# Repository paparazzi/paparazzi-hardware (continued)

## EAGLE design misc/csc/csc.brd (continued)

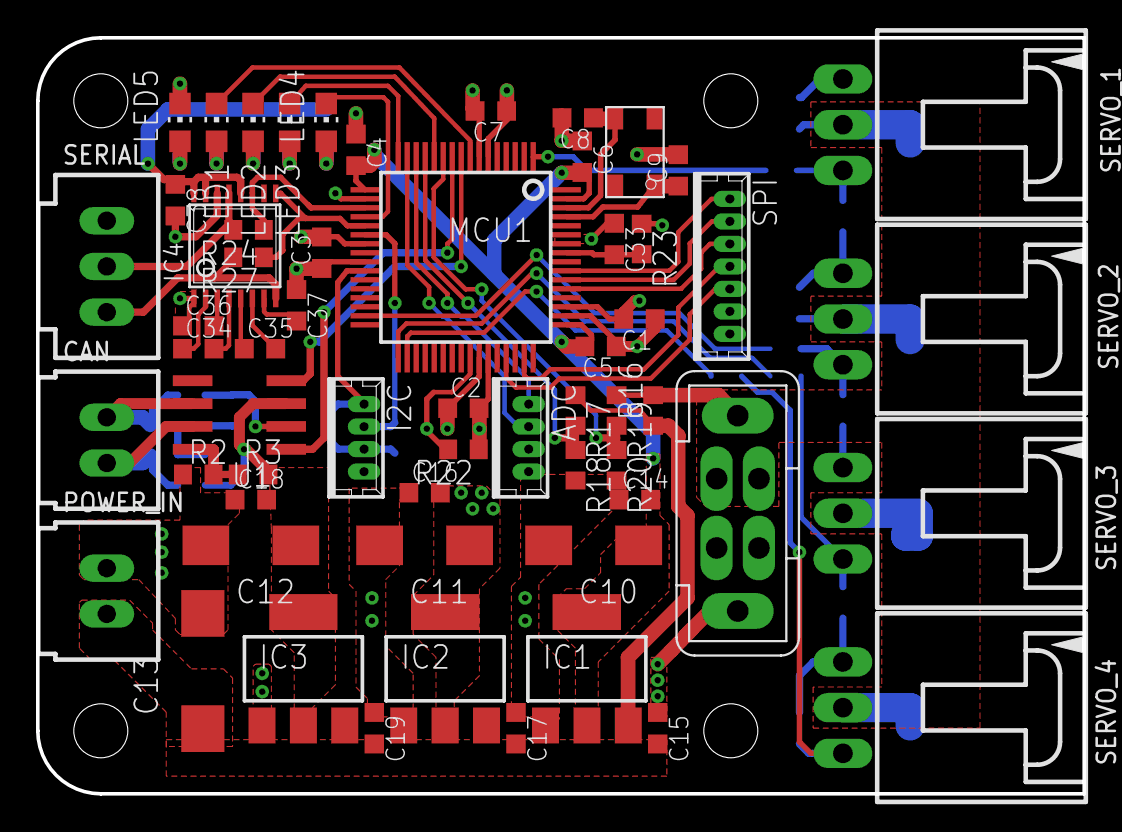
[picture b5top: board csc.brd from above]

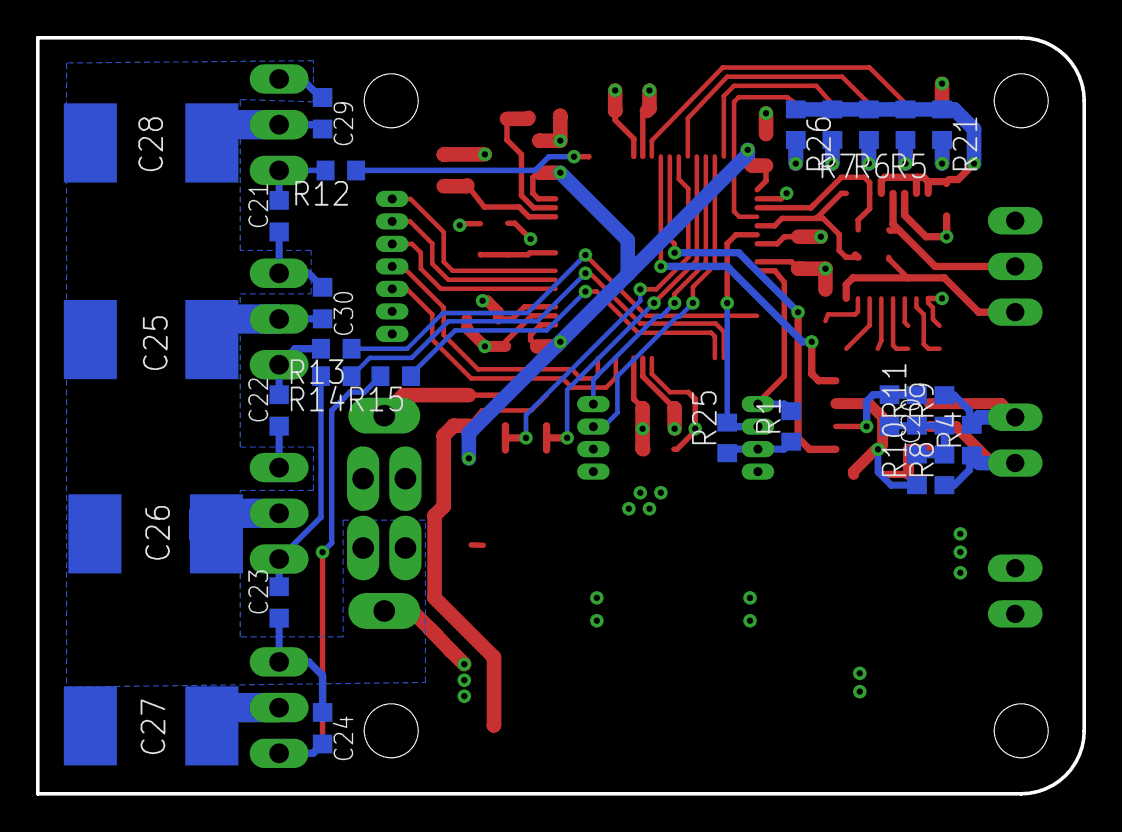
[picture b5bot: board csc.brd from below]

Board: 4 copper layers, 58.1 x 42.0 mm, 87 parts (27 on the bottom side), 55 nets.

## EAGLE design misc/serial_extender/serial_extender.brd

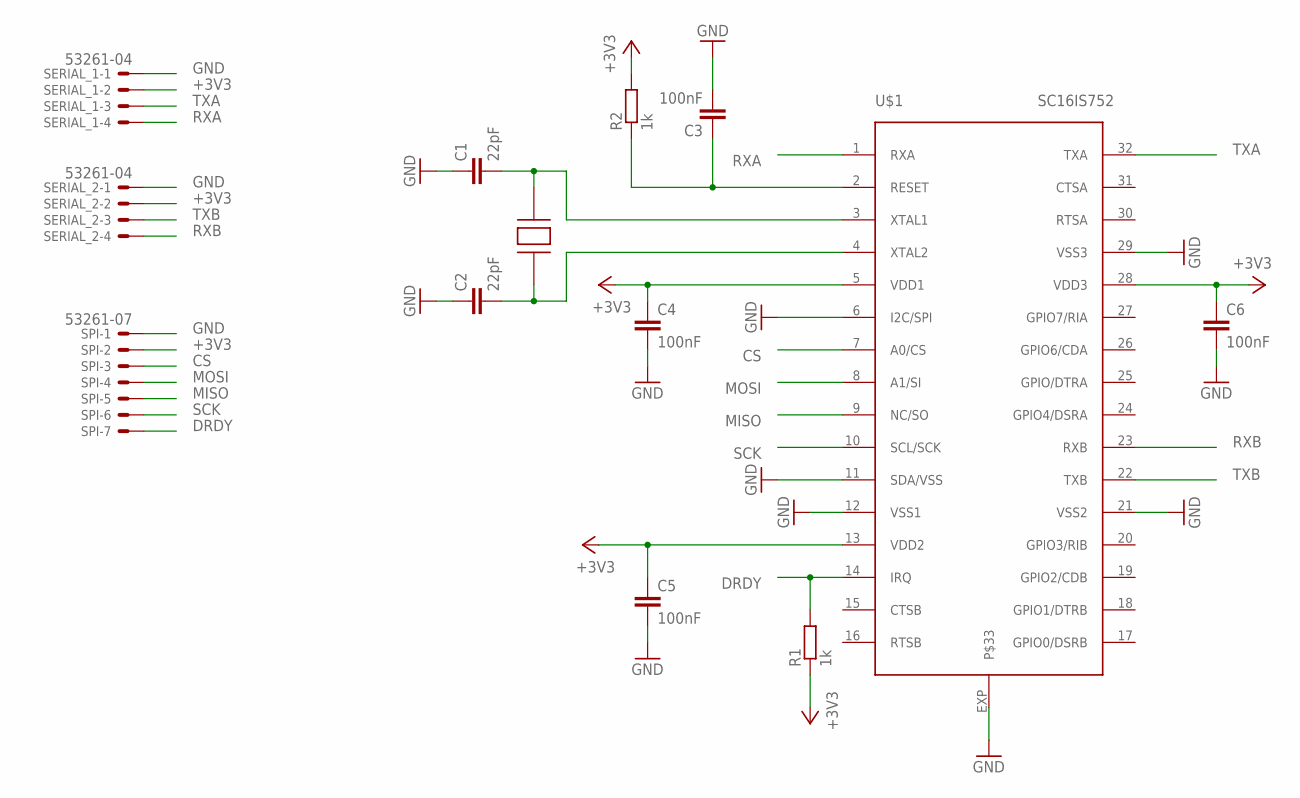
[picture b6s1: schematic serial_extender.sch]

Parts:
C1, C2: 22pF; C0603K
C3, C4, C5, C6: 100nF; C0603K
R1, R2: 1k; R0603
SERIAL_1, SERIAL_2: 53261-04
SPI: 53261-07
U$1: SC16IS752; HVQFN32
U$2: CRYSTAL_CTS; CTS_CRYSTAL

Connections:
+3V3: C4.1, C5.1, C6.1, R1.1, R2.2, SERIAL_1.2, SERIAL_2.2, SPI.2, U$1.5 (VDD1), U$1.13 (VDD2), U$1.28 (VDD3)
CS: SPI.3, U$1.7 (A0/CS)
DRDY: R1.2, SPI.7, U$1.14 (IRQ)
GND: C1.1, C2.1, C3.2, C4.2, C5.2, C6.2, SERIAL_1.1, SERIAL_2.1, SPI.1, U$1.6 (I2C/SPI), U$1.11 (SDA/VSS), U$1.12 (VSS1), U$1.21 (VSS2), U$1.29 (VSS3), U$1.EXP
MISO: SPI.5, U$1.9 (NC/SO)
MOSI: SPI.4, U$1.8 (A1/SI)
unnamed: C1.2, U$1.3 (XTAL1), U$2.P$3
unnamed: C2.2, U$1.4 (XTAL2), U$2.P$1
unnamed: C3.1, R2.1, U$1.2 (RESET)
RXA: SERIAL_1.4, U$1.1 (RXA)
RXB: SERIAL_2.4, U$1.23 (RXB)
SCK: SPI.6, U$1.10 (SCL/SCK)
TXA: SERIAL_1.3, U$1.32 (TXA)
TXB: SERIAL_2.3, U$1.22 (TXB)

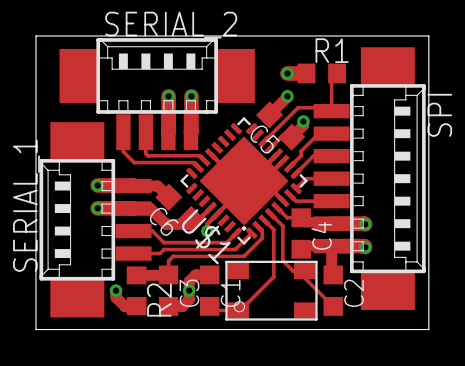
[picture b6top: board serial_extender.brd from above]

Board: 4 copper layers, 21.8 x 16.3 mm, 13 parts (0 on the bottom side), 14 nets.
